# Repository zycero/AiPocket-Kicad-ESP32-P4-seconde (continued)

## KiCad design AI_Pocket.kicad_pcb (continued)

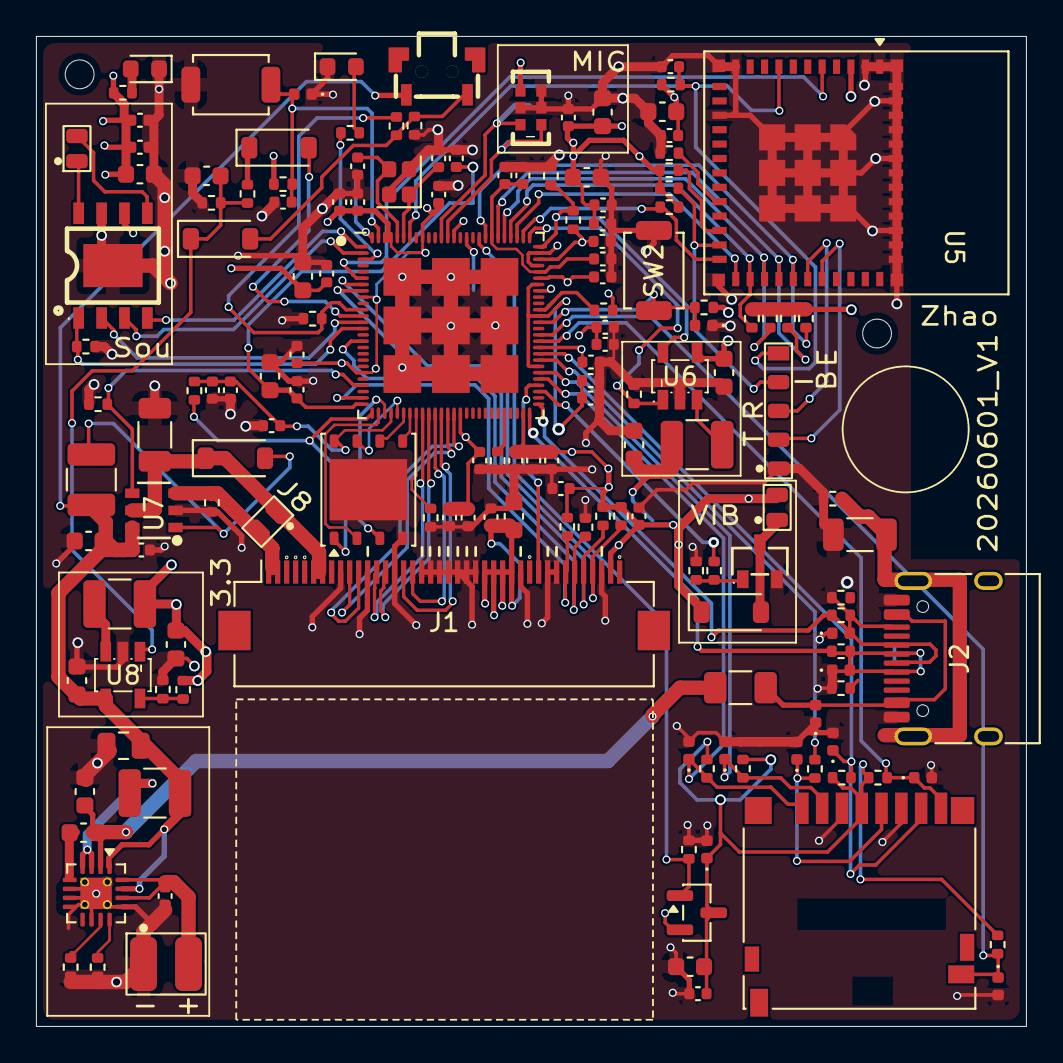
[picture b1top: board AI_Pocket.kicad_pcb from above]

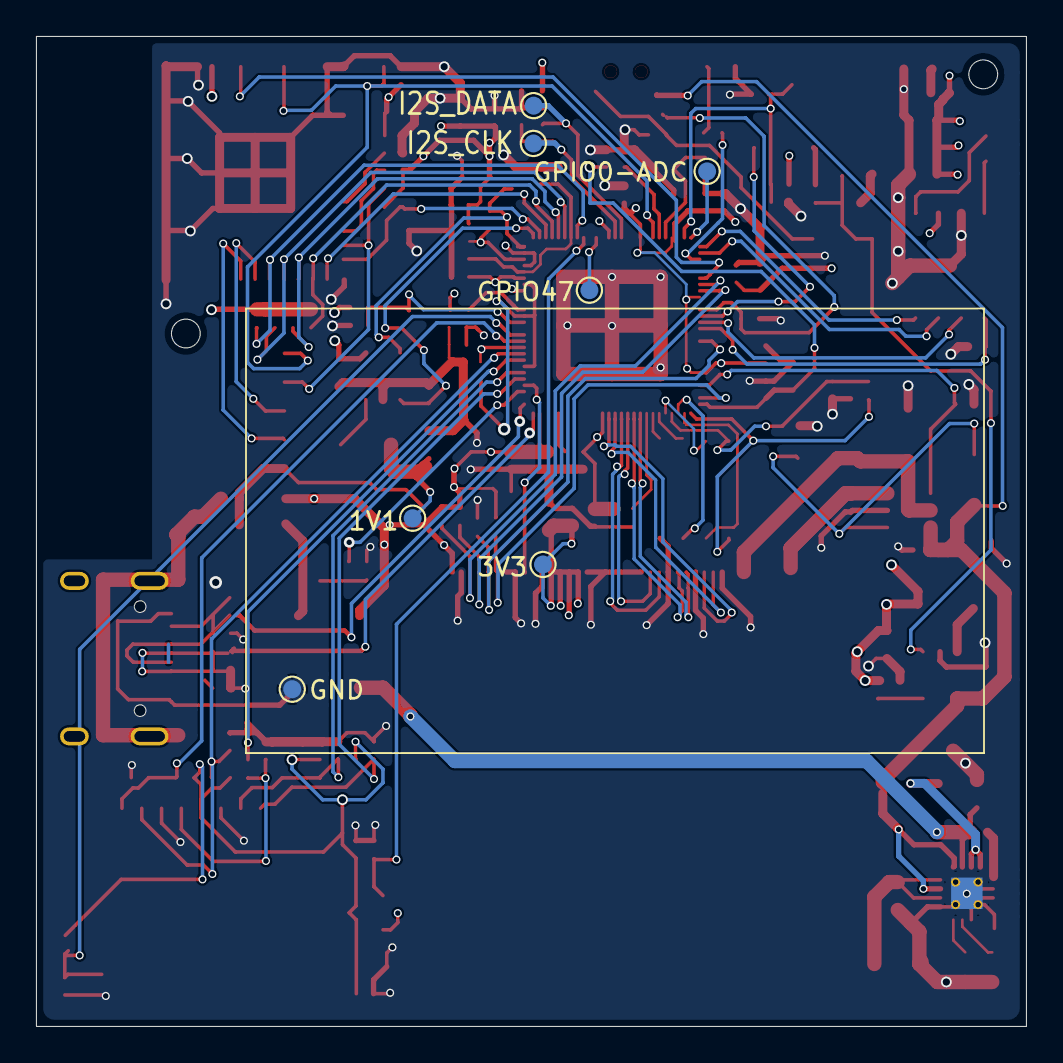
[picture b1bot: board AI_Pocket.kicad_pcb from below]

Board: 4 copper layers, 55.0 x 55.0 mm, 164 parts (7 on the bottom side), 98 nets.
